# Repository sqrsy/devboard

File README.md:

# What is it?

This folder contains miscellaneous PCB parts that I designed to make it easier to prototype Eurorack modules on a breadboard. They are all open to use, but you must make any derivatives open too. If you use them commercially, please donate 10% of profits to a charity nearby you.

# Parts

* chips/flip-flop
	* A Euro-block for the 4013N chip.
* parts/array
	* Use to organize capacitors of various sizes.
* parts/jacks
	* A Euro-block to send or receive signal via 3.5mm jacks.
* parts/pot
	* Use to organize potentiometers.
* parts/power
	* Use to power Euro-blocks.

# Disclaimer

All files are provided without any guarentee. If you notice a mistake, please submit an Issue and I will fix it.

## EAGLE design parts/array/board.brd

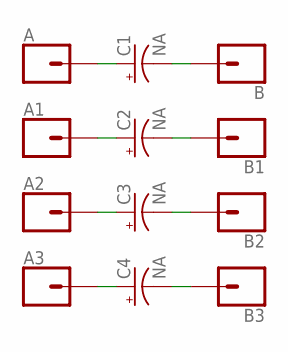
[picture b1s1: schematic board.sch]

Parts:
A, A1, A2, A3: CONN_01; 1X01
B, B1, B2, B3: CONN_01; 1X01
C1, C2, C3, C4: NA; CPOL-RADIAL-2.5MM-5MM

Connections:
unnamed: A.1, C1.1 (+)
unnamed: A1.1, C2.1 (+)
unnamed: A2.1, C3.1 (+)
unnamed: A3.1, C4.1 (+)
unnamed: B3.1, C4.2 (-)
unnamed: B2.1, C3.2 (-)
unnamed: B1.1, C2.2 (-)
unnamed: B.1, C1.2 (-)

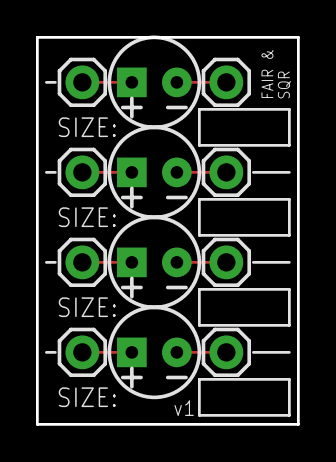
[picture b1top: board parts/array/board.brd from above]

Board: 2 copper layers, 14.5 x 21.5 mm, 12 parts (0 on the bottom side), 8 nets.

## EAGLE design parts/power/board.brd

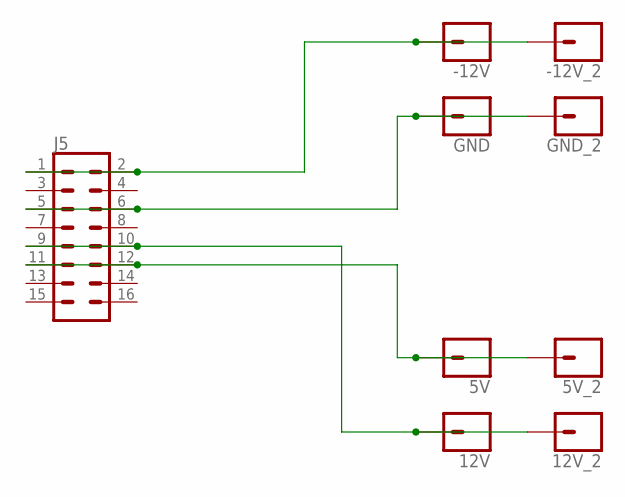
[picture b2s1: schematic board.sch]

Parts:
5V, 5V_2, 12V, 12V_2: CONN_01; 1X01
-12V, -12V_2: CONN_01; 1X01
GND: CONN_01; 1X01
GND_2: CONN_01; 1X01
J5: CONN_08X2; 2X8

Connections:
unnamed: -12V.1, -12V_2.1, J5.1, J5.2
unnamed: GND.1, GND_2.1, J5.5, J5.6
unnamed: 12V.1, 12V_2.1, J5.9, J5.10
unnamed: 5V.1, 5V_2.1, J5.11, J5.12

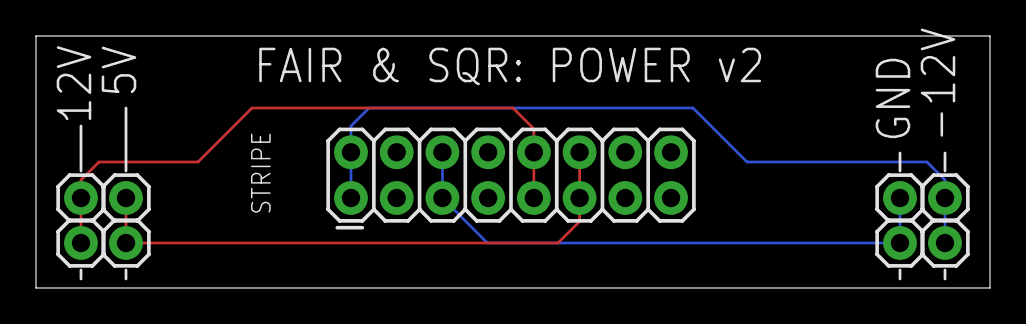
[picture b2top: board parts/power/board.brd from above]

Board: 2 copper layers, 53.0 x 14.0 mm, 9 parts (0 on the bottom side), 4 nets.

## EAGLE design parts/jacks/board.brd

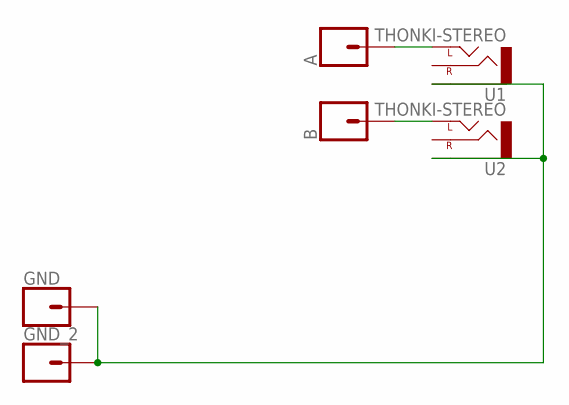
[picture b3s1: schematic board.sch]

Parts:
A: CONN_01; 1X01
B: CONN_01; 1X01
GND: CONN_01; 1X01
GND_2: CONN_01; 1X01
U1, U2: THONKI-STEREO; WQP-PJ366ST_JACK

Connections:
unnamed: A.1, U1.P$1_TIP (LEFT)
unnamed: B.1, U2.P$1_TIP (LEFT)
unnamed: GND.1, GND_2.1, U1.P$3_SLEEVE (SLEEVE), U2.P$3_SLEEVE (SLEEVE)

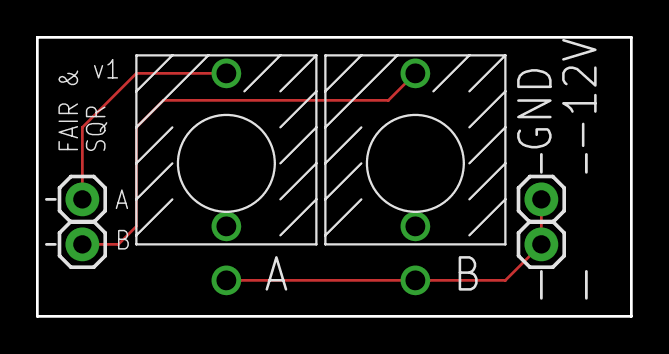
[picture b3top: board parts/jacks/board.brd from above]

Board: 2 copper layers, 33.0 x 15.5 mm, 6 parts (0 on the bottom side), 3 nets.

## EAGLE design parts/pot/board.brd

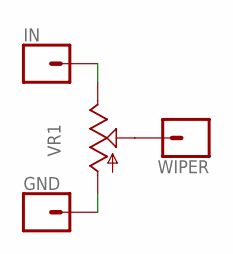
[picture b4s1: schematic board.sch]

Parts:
GND: CONN_01; 1X01
IN: CONN_01; 1X01
VR1: 9MM_SNAP-IN_POT_; 9MM_SNAP-IN_POT
WIPER: CONN_01; 1X01

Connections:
unnamed: IN.1, VR1.3 (E)
unnamed: GND.1, VR1.1 (A)
unnamed: VR1.2 (S), WIPER.1

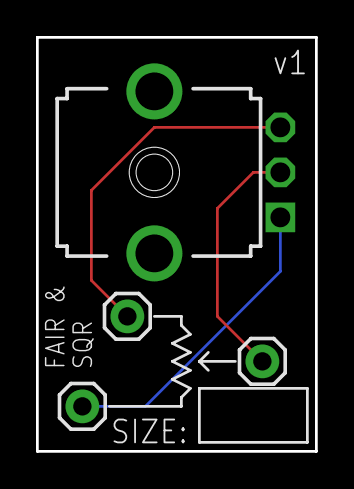
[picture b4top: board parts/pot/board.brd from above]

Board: 2 copper layers, 15.5 x 23.0 mm, 4 parts (0 on the bottom side), 3 nets.

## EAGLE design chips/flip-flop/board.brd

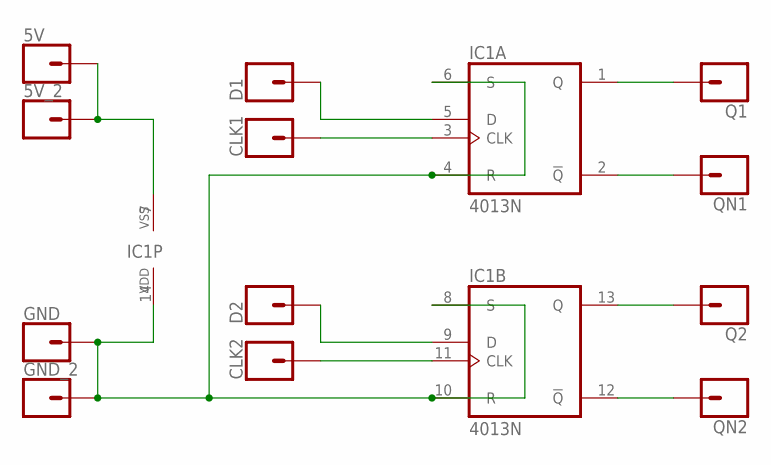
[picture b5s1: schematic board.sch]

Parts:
5V, 5V_2: CONN_01; 1X01
CLK1, CLK2: CONN_01; 1X01
D1, D2: CONN_01; 1X01
GND: CONN_01; 1X01
GND_2: CONN_01; 1X01
IC1: 4013N; DIL14
Q1, Q2: CONN_01; 1X01
QN1, QN2: CONN_01; 1X01

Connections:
unnamed: 5V.1, 5V_2.1, IC1.7 (VSS)
unnamed: D1.1, IC1.5 (D)
unnamed: IC1.13 (Q), Q2.1
unnamed: IC1.1 (Q), Q1.1
unnamed: CLK1.1, IC1.3 (CLK)
unnamed: D2.1, IC1.9 (D)
unnamed: CLK2.1, IC1.11 (CLK)
unnamed: IC1.2 (!Q), QN1.1
unnamed: IC1.12 (!Q), QN2.1
unnamed: GND.1, GND_2.1, IC1.4 (R), IC1.6 (S), IC1.8 (S), IC1.10 (R), IC1.14 (VDD)

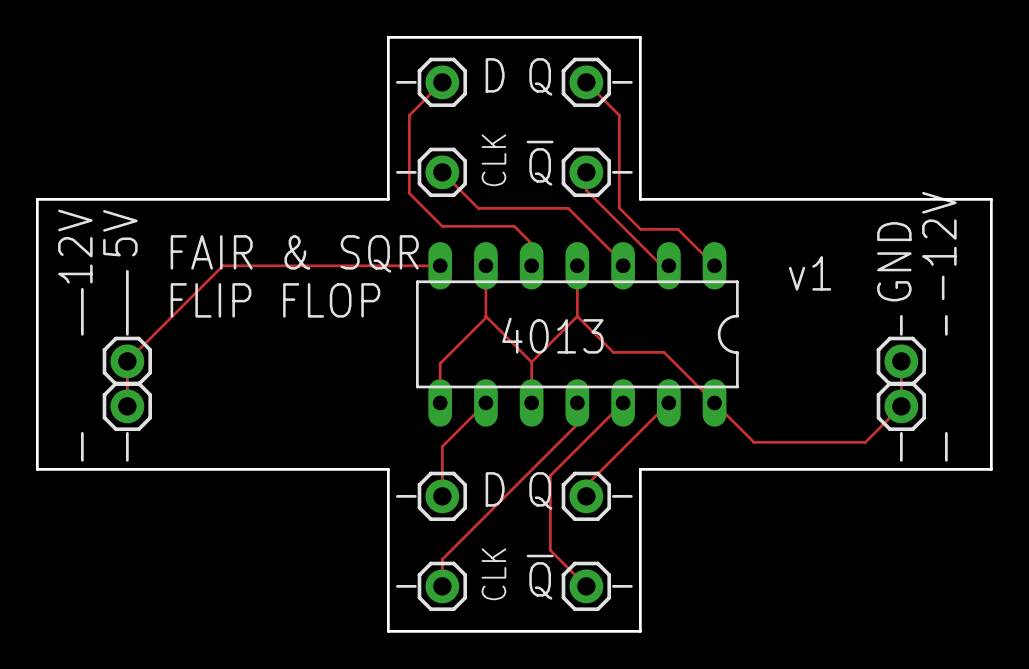
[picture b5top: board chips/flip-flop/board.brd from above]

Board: 2 copper layers, 53.0 x 33.0 mm, 13 parts (0 on the bottom side), 10 nets.

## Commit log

2023-10-08 Launch devboard parts

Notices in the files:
parts and their libraries:
SparkFun-Connectors: Licensing: Creative Commons ShareAlike 4.0 International - https://creativecommons.org/licenses/by-sa/4.0
